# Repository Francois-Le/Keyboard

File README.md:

Complete custom keyboard with pcb design, 3D printable casing and firmware for a raspberry pi pico. Uses kailh low profile switches.

*Warning:* PCB_v2 may have some design mistake, I can't remember if I fixed them.

The firmware in `code/arduino_keyboard` provides HID keyboard output and an
optional binary USB serial trace. See its README for Arduino Mbed Pico build
instructions.

Open `code/remote/index.html` in desktop Chrome or Edge for the Web Serial
debugger: a vertical input/decision/HID timeline with queue inspection. It works
as a local file or a hosted HTTPS page; **Demo trace** works without hardware.
The remote README describes the protocol, capture export/import and development.

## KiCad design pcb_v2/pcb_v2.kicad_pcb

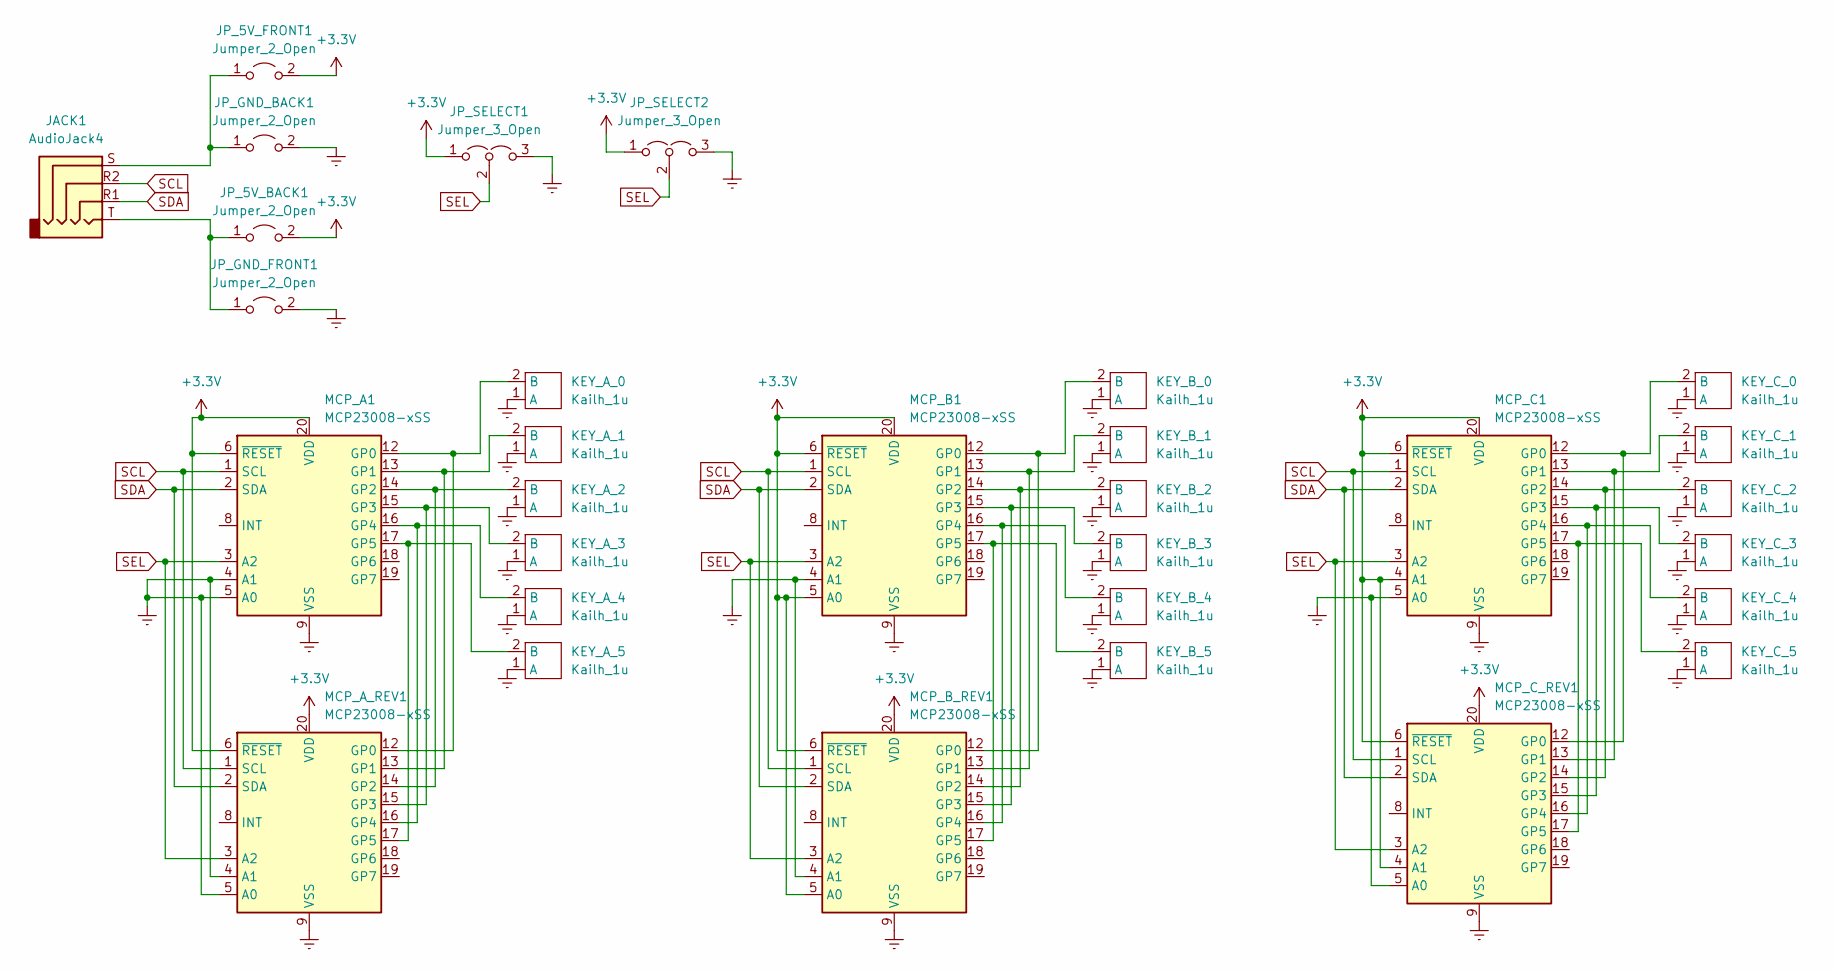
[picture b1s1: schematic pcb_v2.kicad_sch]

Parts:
JACK1: AudioJack4; TRRS-PJ-320A-no-Fmask-reversible
JP_5V_BACK1, JP_5V_FRONT1: Jumper_2_Open; SolderJumper-2_P1.3mm_Open_Pad1.0x1.5mm
JP_GND_BACK1: Jumper_2_Open; SolderJumper-2_P1.3mm_Open_Pad1.0x1.5mm
JP_GND_FRONT1: Jumper_2_Open; SolderJumper-2_P1.3mm_Open_Pad1.0x1.5mm
JP_SELECT1, JP_SELECT2: Jumper_3_Open; SolderJumper-3_P1.3mm_Open_Pad1.0x1.5mm
KEY_A_0, KEY_A_1, KEY_A_2, KEY_A_3, KEY_A_4, KEY_A_5: Kailh_1u; SW_PG1350_reversible
KEY_B_0, KEY_B_1, KEY_B_2, KEY_B_3, KEY_B_4, KEY_B_5: Kailh_1u; SW_PG1350_reversible
KEY_C_0, KEY_C_1, KEY_C_2, KEY_C_3, KEY_C_4, KEY_C_5: Kailh_1u; SW_PG1350_reversible
MCP_A1: MCP23008-xSS; SSOP-20_5.3x7.2mm_P0.65mm
MCP_A_REV1: MCP23008-xSS; SSOP-20_5.3x7.2mm_P0.65mm
MCP_B1: MCP23008-xSS; SSOP-20_5.3x7.2mm_P0.65mm
MCP_B_REV1: MCP23008-xSS; SSOP-20_5.3x7.2mm_P0.65mm
MCP_C1: MCP23008-xSS; SSOP-20_5.3x7.2mm_P0.65mm
MCP_C_REV1: MCP23008-xSS; SSOP-20_5.3x7.2mm_P0.65mm

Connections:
+3V3: JP_5V_BACK1.2 (B), JP_5V_FRONT1.2 (B), JP_SELECT1.1 (A), JP_SELECT2.1 (A), MCP_A1.6 (~RESET), MCP_A1.20 (VDD), MCP_A_REV1.6 (~RESET), MCP_A_REV1.20 (VDD), MCP_B1.5 (A0), MCP_B1.6 (~RESET), MCP_B1.20 (VDD), MCP_B_REV1.5 (A0), MCP_B_REV1.6 (~RESET), MCP_B_REV1.20 (VDD), MCP_C1.4 (A1), MCP_C1.6 (~RESET), MCP_C1.20 (VDD), MCP_C_REV1.4 (A1), MCP_C_REV1.6 (~RESET), MCP_C_REV1.20 (VDD)
Earth: JP_GND_BACK1.2 (B), JP_GND_FRONT1.2 (B), JP_SELECT1.3 (B), JP_SELECT2.3 (B), KEY_A_0.1 (A), KEY_A_1.1 (A), KEY_A_2.1 (A), KEY_A_3.1 (A), KEY_A_4.1 (A), KEY_A_5.1 (A), KEY_B_0.1 (A), KEY_B_1.1 (A), KEY_B_2.1 (A), KEY_B_3.1 (A), KEY_B_4.1 (A), KEY_B_5.1 (A), KEY_C_0.1 (A), KEY_C_1.1 (A), KEY_C_2.1 (A), KEY_C_3.1 (A), KEY_C_4.1 (A), KEY_C_5.1 (A), MCP_A1.4 (A1), MCP_A1.5 (A0), MCP_A1.9 (VSS), MCP_A_REV1.4 (A1), MCP_A_REV1.5 (A0), MCP_A_REV1.9 (VSS), MCP_B1.4 (A1), MCP_B1.9 (VSS), MCP_B_REV1.4 (A1), MCP_B_REV1.9 (VSS), MCP_C1.5 (A0), MCP_C1.9 (VSS), MCP_C_REV1.5 (A0), MCP_C_REV1.9 (VSS)
unnamed: JACK1.S, JP_5V_FRONT1.1 (A), JP_GND_BACK1.1 (A)
unnamed: JACK1.T, JP_5V_BACK1.1 (A), JP_GND_FRONT1.1 (A)
unnamed: KEY_A_0.2 (B), MCP_A1.12 (GP0), MCP_A_REV1.12 (GP0)
unnamed: KEY_A_1.2 (B), MCP_A1.13 (GP1), MCP_A_REV1.13 (GP1)
unnamed: KEY_A_2.2 (B), MCP_A1.14 (GP2), MCP_A_REV1.14 (GP2)
unnamed: KEY_A_3.2 (B), MCP_A1.15 (GP3), MCP_A_REV1.15 (GP3)
unnamed: KEY_A_4.2 (B), MCP_A1.16 (GP4), MCP_A_REV1.16 (GP4)
unnamed: KEY_A_5.2 (B), MCP_A1.17 (GP5), MCP_A_REV1.17 (GP5)
unnamed: KEY_B_0.2 (B), MCP_B1.12 (GP0), MCP_B_REV1.12 (GP0)
unnamed: KEY_B_1.2 (B), MCP_B1.13 (GP1), MCP_B_REV1.13 (GP1)
unnamed: KEY_B_2.2 (B), MCP_B1.14 (GP2), MCP_B_REV1.14 (GP2)
unnamed: KEY_B_3.2 (B), MCP_B1.15 (GP3), MCP_B_REV1.15 (GP3)
unnamed: KEY_B_4.2 (B), MCP_B1.16 (GP4), MCP_B_REV1.16 (GP4)
unnamed: KEY_B_5.2 (B), MCP_B1.17 (GP5), MCP_B_REV1.17 (GP5)
unnamed: KEY_C_0.2 (B), MCP_C1.12 (GP0), MCP_C_REV1.12 (GP0)
unnamed: KEY_C_1.2 (B), MCP_C1.13 (GP1), MCP_C_REV1.13 (GP1)
unnamed: KEY_C_2.2 (B), MCP_C1.14 (GP2), MCP_C_REV1.14 (GP2)
unnamed: KEY_C_3.2 (B), MCP_C1.15 (GP3), MCP_C_REV1.15 (GP3)
unnamed: KEY_C_4.2 (B), MCP_C1.16 (GP4), MCP_C_REV1.16 (GP4)
unnamed: KEY_C_5.2 (B), MCP_C1.17 (GP5), MCP_C_REV1.17 (GP5)
SCL: JACK1.R2, MCP_A1.1 (SCL), MCP_A_REV1.1 (SCL), MCP_B1.1 (SCL), MCP_B_REV1.1 (SCL), MCP_C1.1 (SCL), MCP_C_REV1.1 (SCL)
SDA: JACK1.R1, MCP_A1.2 (SDA), MCP_A_REV1.2 (SDA), MCP_B1.2 (SDA), MCP_B_REV1.2 (SDA), MCP_C1.2 (SDA), MCP_C_REV1.2 (SDA)
SEL: JP_SELECT1.2 (C), JP_SELECT2.2 (C), MCP_A1.3 (A2), MCP_A_REV1.3 (A2), MCP_B1.3 (A2), MCP_B_REV1.3 (A2), MCP_C1.3 (A2), MCP_C_REV1.3 (A2)

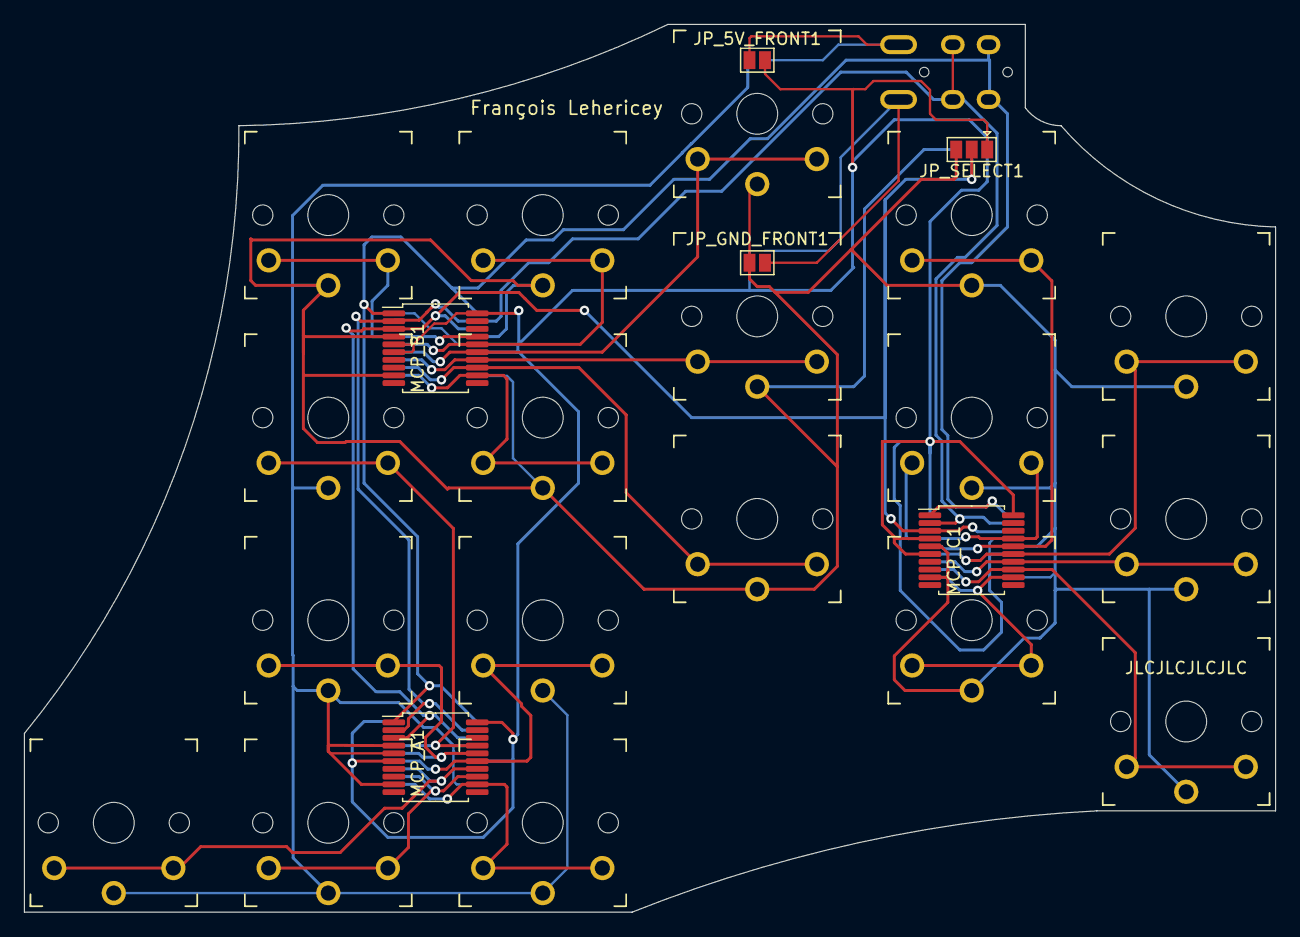
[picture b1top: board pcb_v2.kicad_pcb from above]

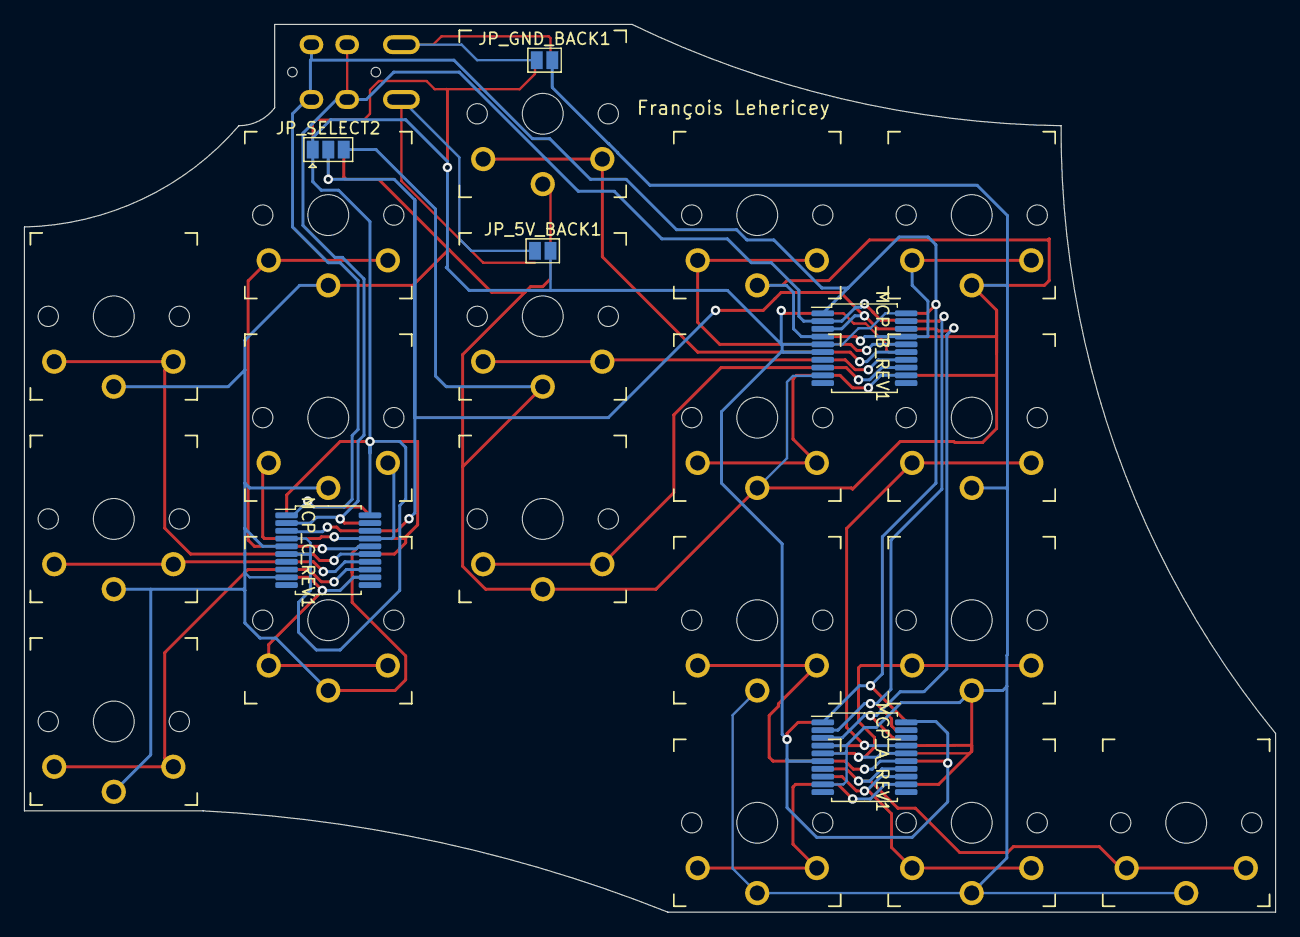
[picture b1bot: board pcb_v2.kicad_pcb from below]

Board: 2 copper layers, 105.0 x 74.5 mm, 31 parts (6 on the bottom side), 25 nets.

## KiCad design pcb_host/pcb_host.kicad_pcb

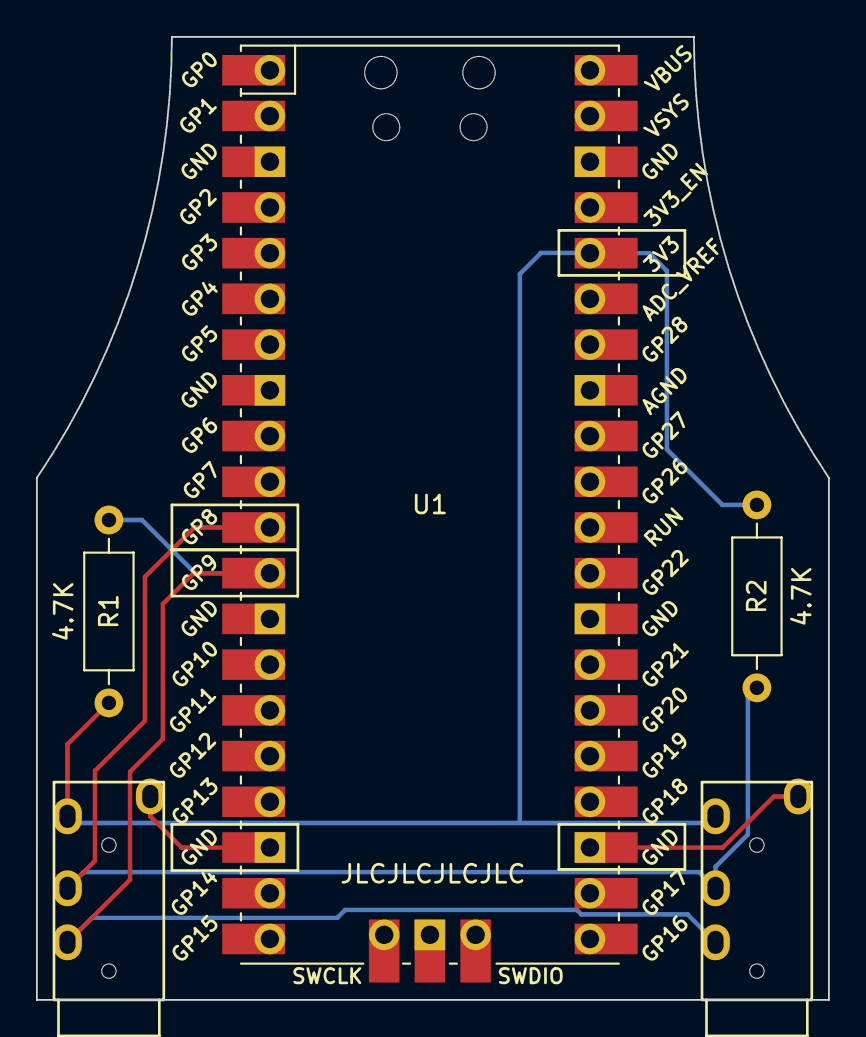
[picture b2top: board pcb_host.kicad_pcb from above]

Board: 2 copper layers, 44.0 x 53.5 mm, 5 parts (0 on the bottom side), 5 nets.

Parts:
J1, J2: AudioJack4; TRRS-PJ-320A-no-Fmask
R1, R2: 4.7K; R_Axial_DIN0207_L6.3mm_D2.5mm_P10.16mm_Horizontal
U1: Pico; RPi_Pico_SMD_TH

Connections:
unnamed: J2.S, U1.23 (GND)
unnamed: J1.T, J2.T, R1.1, R2.1, U1.36 (3V3)
unnamed: J1.S, U1.18 (GND)
SCL: J1.R2, J2.R2, R1.2, U1.12 (GPIO9)
SDA: J1.R1, J2.R1, R2.2, U1.11 (GPIO8)

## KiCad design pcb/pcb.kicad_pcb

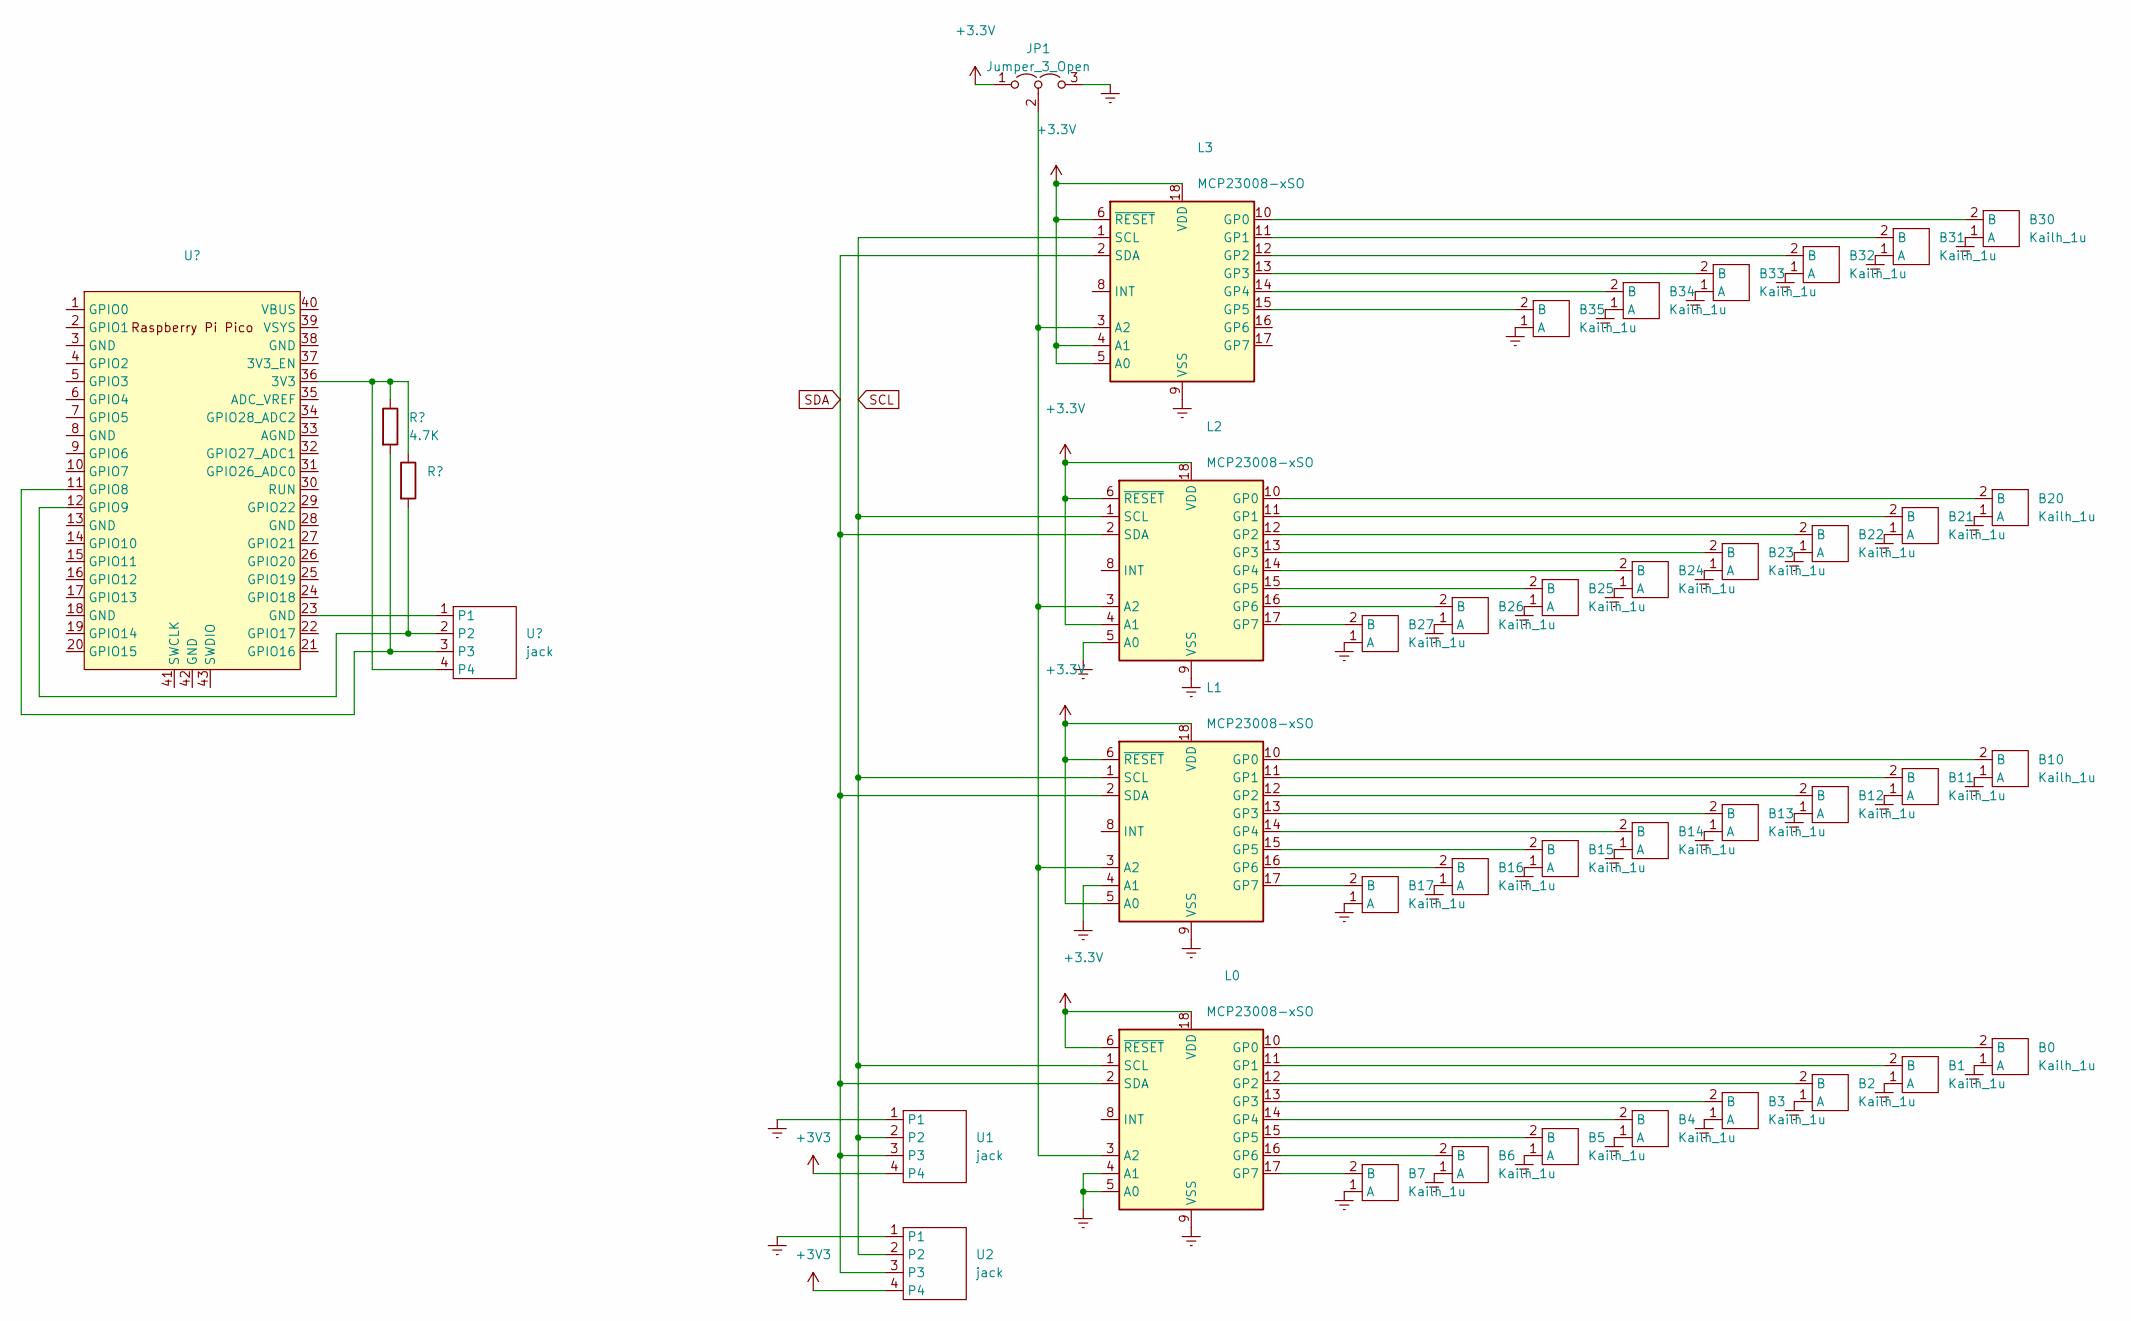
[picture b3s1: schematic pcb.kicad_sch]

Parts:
B0, B1, B2, B3, B4, B5, B6, B7, B10, B11, B12, B13, B14, B15, B16, B17, B20, B21, B22, B23, B24, B25, B26, B27, B30, B31, B32, B33, B34, B35: Kailh_1u; SW_Kailh_Choc_V1_1.00u
JP1: Jumper_3_Open; SolderJumper-3_P1.3mm_Open_RoundedPad1.0x1.5mm
L0, L1, L2, L3: MCP23008-xSO; SOIC-18W_7.5x11.6mm_P1.27mm
U1, U2: jack

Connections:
Earth: B0.1 (A), B1.1 (A), B2.1 (A), B3.1 (A), B4.1 (A), B5.1 (A), B6.1 (A), B7.1 (A), B10.1 (A), B11.1 (A), B12.1 (A), B13.1 (A), B14.1 (A), B15.1 (A), B16.1 (A), B17.1 (A), B20.1 (A), B21.1 (A), B22.1 (A), B23.1 (A), B24.1 (A), B25.1 (A), B26.1 (A), B27.1 (A), B30.1 (A), B31.1 (A), B32.1 (A), B33.1 (A), B34.1 (A), B35.1 (A), JP1.3 (B), L0.4 (A1), L0.5 (A0), L0.9 (VSS), L1.4 (A1), L1.9 (VSS), L2.5 (A0), L2.9 (VSS), L3.9 (VSS), U1.1, U2.1; also elsewhere on the board
unnamed: B0.2 (B), L0.10 (GP0)
unnamed: B1.2 (B), L0.11 (GP1)
unnamed: B2.2 (B), L0.12 (GP2)
unnamed: B3.2 (B), L0.13 (GP3)
unnamed: B4.2 (B), L0.14 (GP4)
unnamed: B5.2 (B), L0.15 (GP5)
unnamed: B6.2 (B), L0.16 (GP6)
unnamed: B7.2 (B), L0.17 (GP7)
unnamed: B10.2 (B), L1.10 (GP0)
unnamed: B11.2 (B), L1.11 (GP1)
unnamed: B12.2 (B), L1.12 (GP2)
unnamed: B13.2 (B), L1.13 (GP3)
unnamed: B14.2 (B), L1.14 (GP4)
unnamed: B15.2 (B), L1.15 (GP5)
unnamed: B16.2 (B), L1.16 (GP6)
unnamed: B17.2 (B), L1.17 (GP7)
unnamed: B20.2 (B), L2.10 (GP0)
unnamed: B21.2 (B), L2.11 (GP1)
unnamed: B22.2 (B), L2.12 (GP2)
unnamed: B23.2 (B), L2.13 (GP3)
unnamed: B24.2 (B), L2.14 (GP4)
unnamed: B25.2 (B), L2.15 (GP5)
unnamed: B26.2 (B), L2.16 (GP6)
unnamed: B27.2 (B), L2.17 (GP7)
unnamed: B30.2 (B), L3.10 (GP0)
unnamed: B31.2 (B), L3.11 (GP1)
unnamed: B32.2 (B), L3.12 (GP2)
unnamed: B33.2 (B), L3.13 (GP3)
unnamed: B34.2 (B), L3.14 (GP4)
unnamed: B35.2 (B), L3.15 (GP5)
unnamed 31: JP1.2 (C), L0.3 (A2), L1.3 (A2), L2.3 (A2), L3.3 (A2); also elsewhere on the board
SCL: L0.1 (SCL), L1.1 (SCL), L2.1 (SCL), L3.1 (SCL), U1.2, U2.2
SDA: L0.2 (SDA), L1.2 (SDA), L2.2 (SDA), L3.2 (SDA), U1.3, U2.3

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
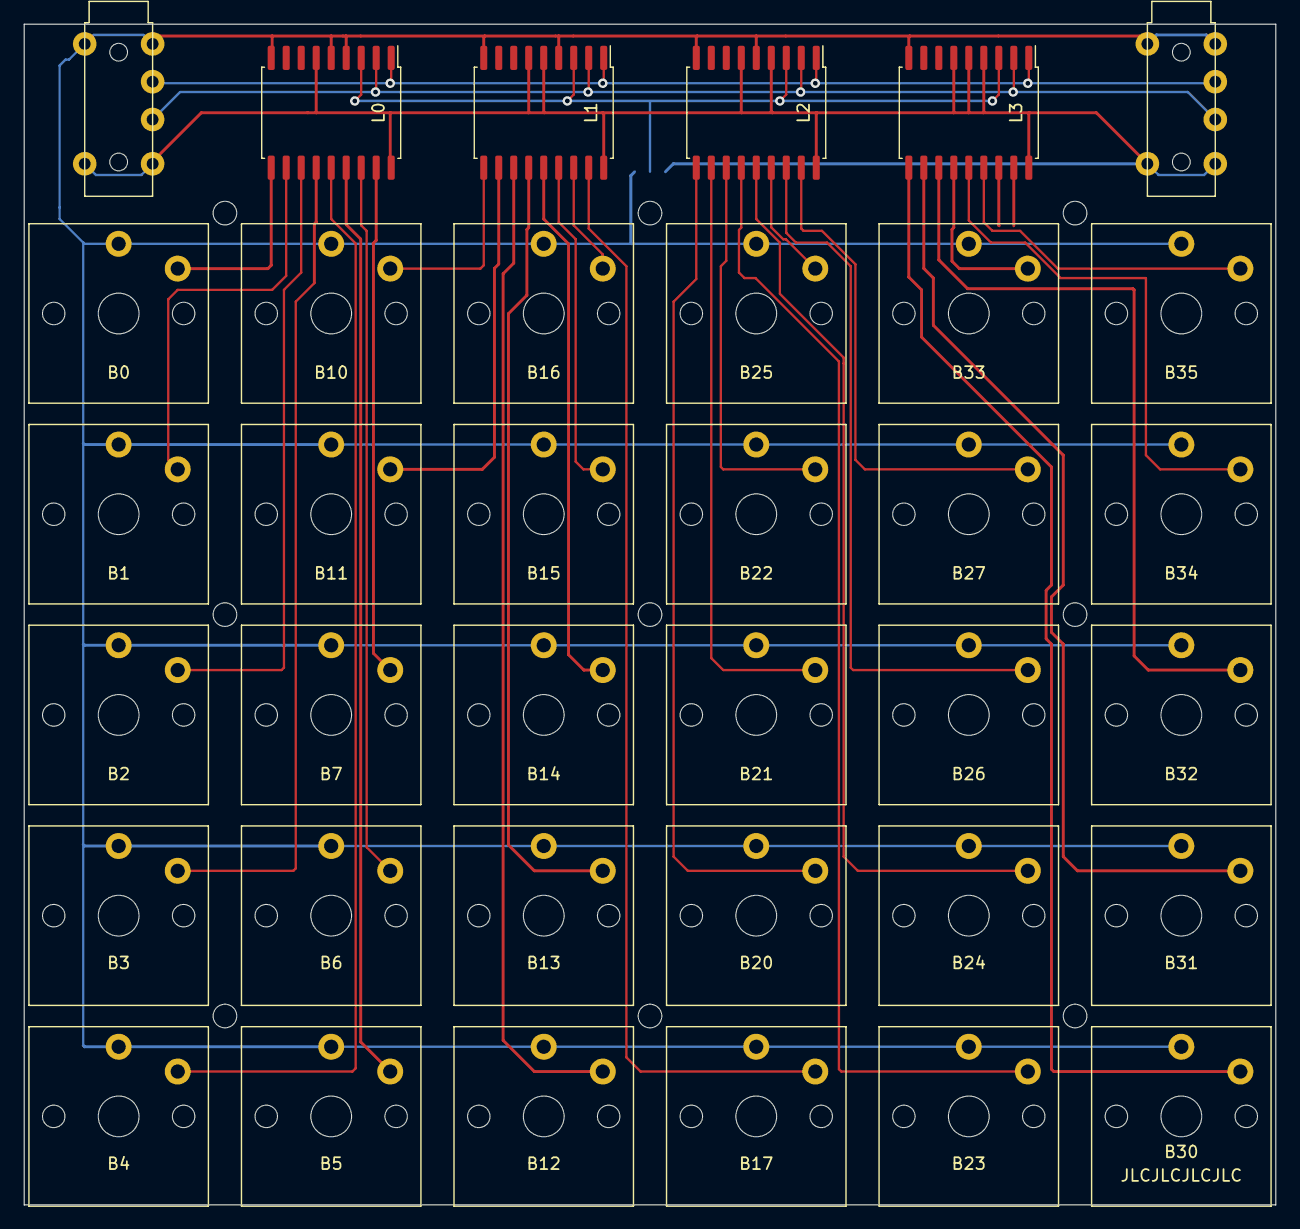
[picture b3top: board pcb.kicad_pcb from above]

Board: 2 copper layers, 106.0 x 100.0 mm, 37 parts (1 on the bottom side), 35 nets.

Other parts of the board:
Left/right selection: Jumper_3_Open; SolderJumper-3_P1.3mm_Open_RoundedPad1.0x1.5mm

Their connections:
Earth: Left/right selection.3 (B); also elsewhere on the board
unnamed 31: Left/right selection.2 (C); also elsewhere on the board

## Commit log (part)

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2022-10-10 Import to git
2022-10-10 Split code in several files + add mutex on event queue
2022-10-24 update key layout
2022-10-29 update layout
2022-11-04 Swap location of square and curly brackets
2022-11-12 Remove usage of the three side keys
2022-11-13 WIP new PCB
2022-11-13 WIP second board
2022-11-14 remove some backup files
2022-11-14 move windows key
2022-11-14 remove backup files
2022-11-15 add pcb host pcb
2022-11-15 update pcb for host
2022-11-29 pcb v2 fixes + support for v2 in firmware
2023-01-10 Add 3d component models on PCB
2023-01-11 enclosure for v2
2023-01-22 Final
2023-10-22 Revert "Merge branch 'multi-core' into main"
    This reverts commit 98082139902066240b697b9f0432adf0479ba885, reversing
    changes made to 2e37bbca62585b6878b8854fa4573379c4c96814.
2025-02-17 Move general config to config.h
2025-02-17 Move some of the event handling code to event.h/cpp
2025-02-18 Move the circular queue implementation in event.h/cpp
2025-02-18 Rename circular buffer class name
2025-02-19 Add a proper iterator type
2025-02-19 Add ranged for loops
2025-02-20 Move the input system to input.h/cpp
2025-02-20 Clean-up input code
2025-02-20 Move some code to keyboard.h/cpp
2025-02-21 Some docs
2025-02-22 Clean up keyboard output interface
2025-02-23 Rework how "on release" keys are handled
2025-02-25 Add event overlap removal
2025-02-25 Add extra comment
2025-02-27 Fix DEBUG_LOG compilation issues
2025-02-27 Bugfix and disable overlap removal that is causing issues
2025-02-28 Fix bugs for "on release" events
2025-05-26 Add key to hold space and move "_"
2025-07-29 Add media key controls
2025-08-03 Minor
